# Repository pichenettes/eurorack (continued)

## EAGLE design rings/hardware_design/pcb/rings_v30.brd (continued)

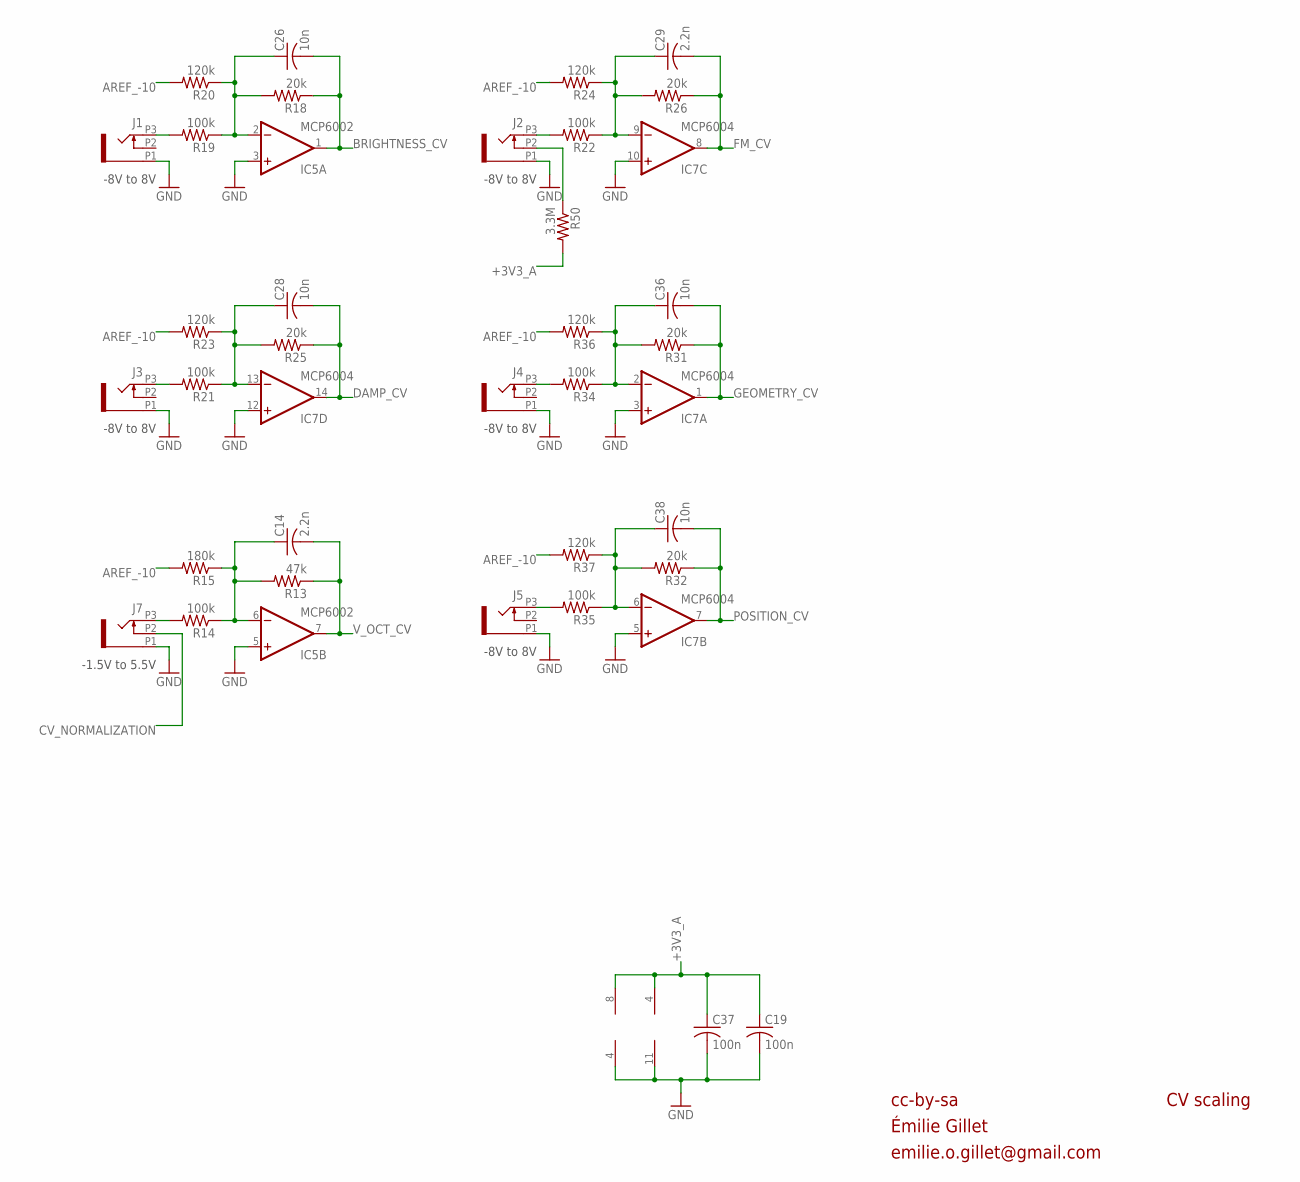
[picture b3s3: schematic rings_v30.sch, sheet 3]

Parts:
C14, C29: 2.2n; C0603
C19, C37: 100n; C0603
C26, C28, C36, C38: 10n; C0603
IC5: MCP6002; SO08
IC7: MCP6004; SO14
J1, J2, J3, J4, J5, J7: PJ301_THONKICONN6; WQP_PJ_301M6
R13: 47k; R0603
R14, R19, R21, R22, R34, R35: 100k; R0603
R15: 180k; R0603
R18, R25, R26, R31, R32: 20k; R0603
R20, R23, R24, R36, R37: 120k; R0603
R50: 3.3M; R0603

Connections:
+3V3_A: C19.1, C37.1, IC5.8 (V+), IC7.4 (V+), R50.2; also elsewhere on the board
AREF_-10: R15.2, R20.2, R23.2, R24.2, R36.2, R37.2; also elsewhere on the board
BRIGHTNESS_CV: C26.2, IC5.1 (OUT), R18.1; also elsewhere on the board
CV_NORMALIZATION: J7.P2 (2); also elsewhere on the board
DAMP_CV: C28.2, IC7.14 (OUT), R25.1; also elsewhere on the board
FM_CV: C29.2, IC7.8 (OUT), R26.1; also elsewhere on the board
GEOMETRY_CV: C36.2, IC7.1 (OUT), R31.1; also elsewhere on the board
GND: C19.2, C37.2, IC5.3 (+IN), IC5.4 (V-), IC5.5 (+IN), IC7.3 (+IN), IC7.5 (+IN), IC7.10 (+IN), IC7.11 (V-), IC7.12 (+IN), J1.P1 (1), J2.P1 (1), J3.P1 (1), J4.P1 (1), J5.P1 (1), J7.P1 (1); also elsewhere on the board
unnamed: J1.P3 (3), R19.2
unnamed: C26.1, IC5.2 (-IN), R18.2, R19.1, R20.1
unnamed: J7.P3 (3), R14.2
unnamed: J2.P3 (3), R22.2
unnamed: C29.1, IC7.9 (-IN), R22.1, R24.1, R26.2
unnamed: J4.P3 (3), R34.2
unnamed: J3.P3 (3), R21.2
unnamed: C28.1, IC7.13 (-IN), R21.1, R23.1, R25.2
unnamed: C14.1, IC5.6 (-IN), R13.2, R14.1, R15.1
unnamed: C36.1, IC7.2 (-IN), R31.2, R34.1, R36.1
unnamed: J5.P3 (3), R35.2
unnamed: C38.1, IC7.6 (-IN), R32.2, R35.1, R37.1
unnamed: J2.P2 (2), R50.1
POSITION_CV: C38.2, IC7.7 (OUT), R32.1; also elsewhere on the board
V_OCT_CV: C14.2, IC5.7 (OUT), R13.1; also elsewhere on the board

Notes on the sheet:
cc-by-sa
CV scaling
-8V to 8V
-1.5V to 5.5V
Émilie Gillet
emilie.o.gillet@gmail.com

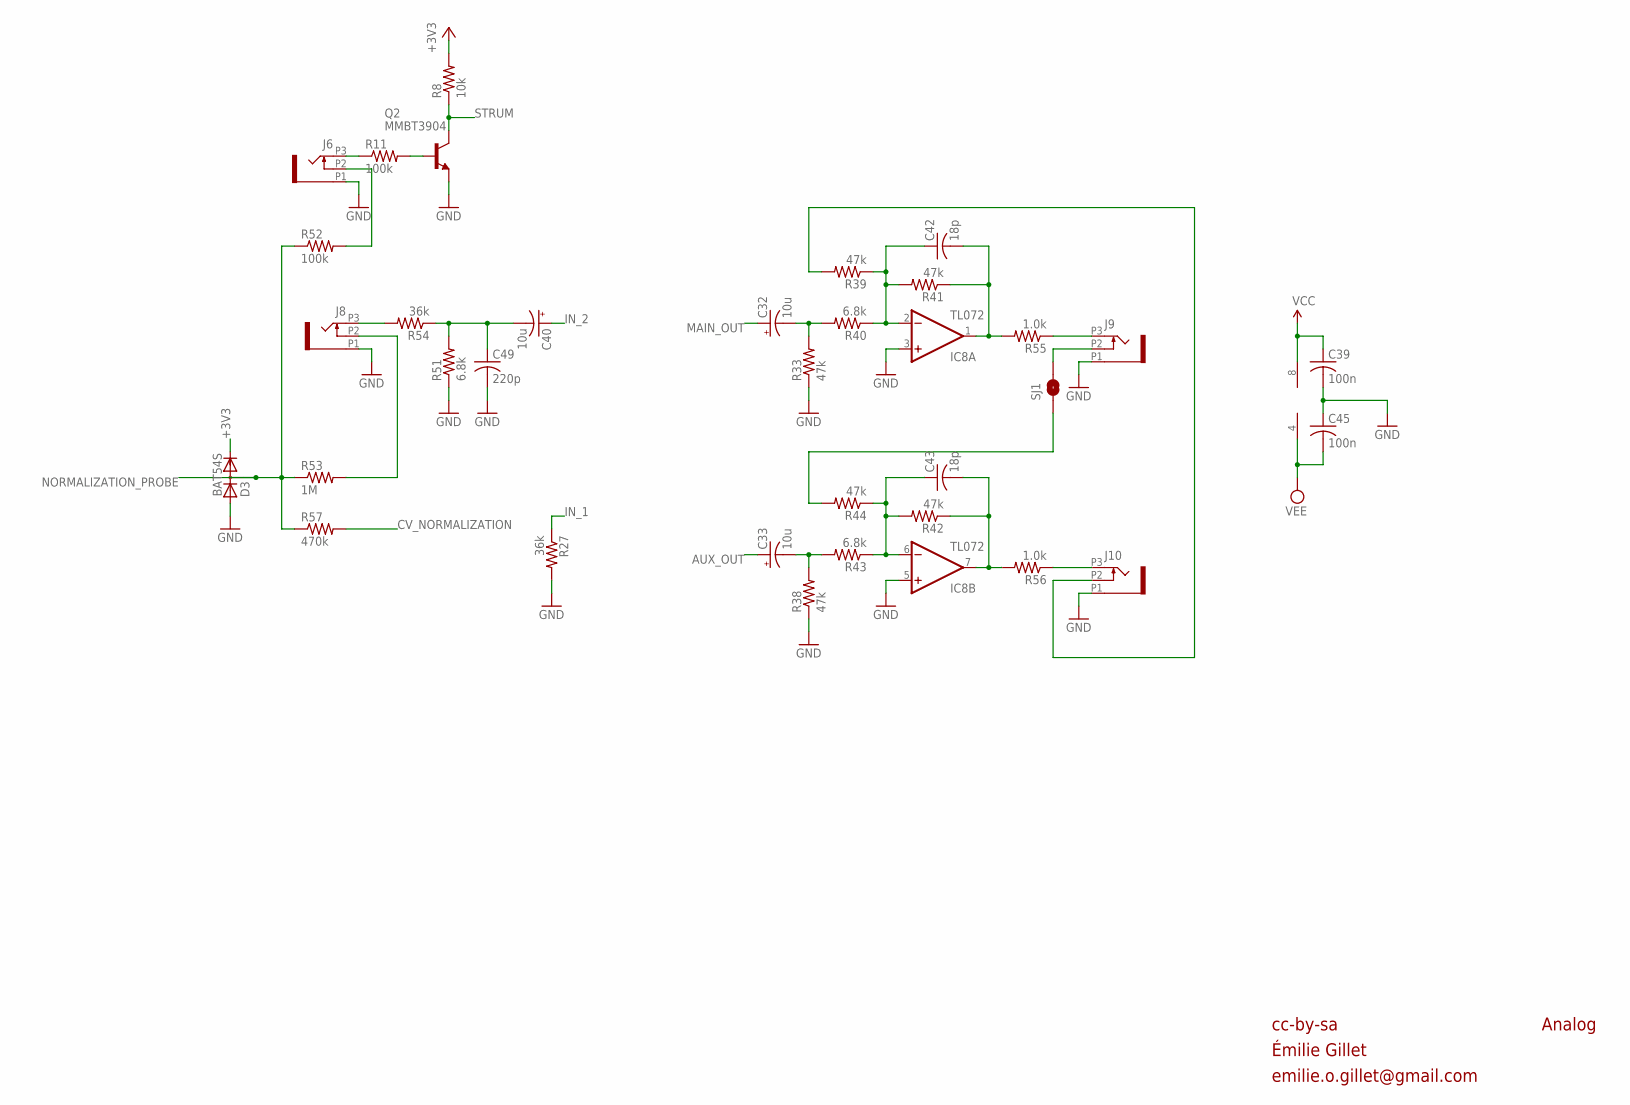
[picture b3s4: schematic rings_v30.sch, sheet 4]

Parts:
C32, C33, C40: 10u; PANASONIC_A
C39, C45: 100n; C0603
C42, C43: 18p; C0603
C49: 220p; C0603
D3: BAT54S; SOT23
IC8: TL072; SO08
J6, J8, J9, J10: PJ301_THONKICONN6; WQP_PJ_301M6
Q2: MMBT3904; SOT23-BEC
R8: 10k; R0603
R11, R52: 100k; R0603
R27, R54: 36k; R0603
R33, R38, R39, R41, R42, R44: 47k; R0603
R40, R43, R51: 6.8k; R0603
R53: 1M; R0603
R55, R56: 1.0k; R0603
R57: 470k; R0603
SJ1: SOLDERJUMPERNC2; SJ_2S-NOTRACE

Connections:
+3V3: D3.2 (C), R8.2; also elsewhere on the board
AUX_OUT: C33.+; also elsewhere on the board
CV_NORMALIZATION: R57.2; also elsewhere on the board
GND: C39.2, C45.1, C49.2, D3.1 (A), IC8.3 (+IN), IC8.5 (+IN), J6.P1 (1), J8.P1 (1), J9.P1 (1), J10.P1 (1), Q2.E, R27.2, R33.1, R38.1, R51.1; also elsewhere on the board
IN_1: R27.1; also elsewhere on the board
IN_2: C40.+; also elsewhere on the board
MAIN_OUT: C32.+; also elsewhere on the board
unnamed: J6.P3 (3), R11.1
unnamed: C40.-, C49.1, R51.2, R54.1
unnamed: J6.P2 (2), R52.2
unnamed: J8.P3 (3), R54.2
unnamed: C33.-, R38.2, R43.2
unnamed: C43.1, IC8.6 (-IN), R42.2, R43.1, R44.1
unnamed: C43.2, IC8.7 (OUT), R42.1, R56.2
unnamed: J10.P3 (3), R56.1
unnamed: C32.-, R33.2, R40.2
unnamed: C42.1, IC8.2 (-IN), R39.1, R40.1, R41.2
unnamed: C42.2, IC8.1 (OUT), R41.1, R55.2
unnamed: J9.P3 (3), R55.1
unnamed: J8.P2 (2), R53.2
unnamed: J10.P2 (2), R39.2
unnamed: R44.2, SJ1.1
unnamed: J9.P2 (2), SJ1.2
unnamed: Q2.B, R11.2
NORMALIZATION_PROBE: D3.3 (AC), R52.1, R53.1, R57.1; also elsewhere on the board
STRUM: Q2.C, R8.1; also elsewhere on the board
VCC: C39.1, IC8.8 (V+); also elsewhere on the board
VEE: C45.2, IC8.4 (V-); also elsewhere on the board

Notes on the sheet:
cc-by-sa
Analog
Émilie Gillet
emilie.o.gillet@gmail.com

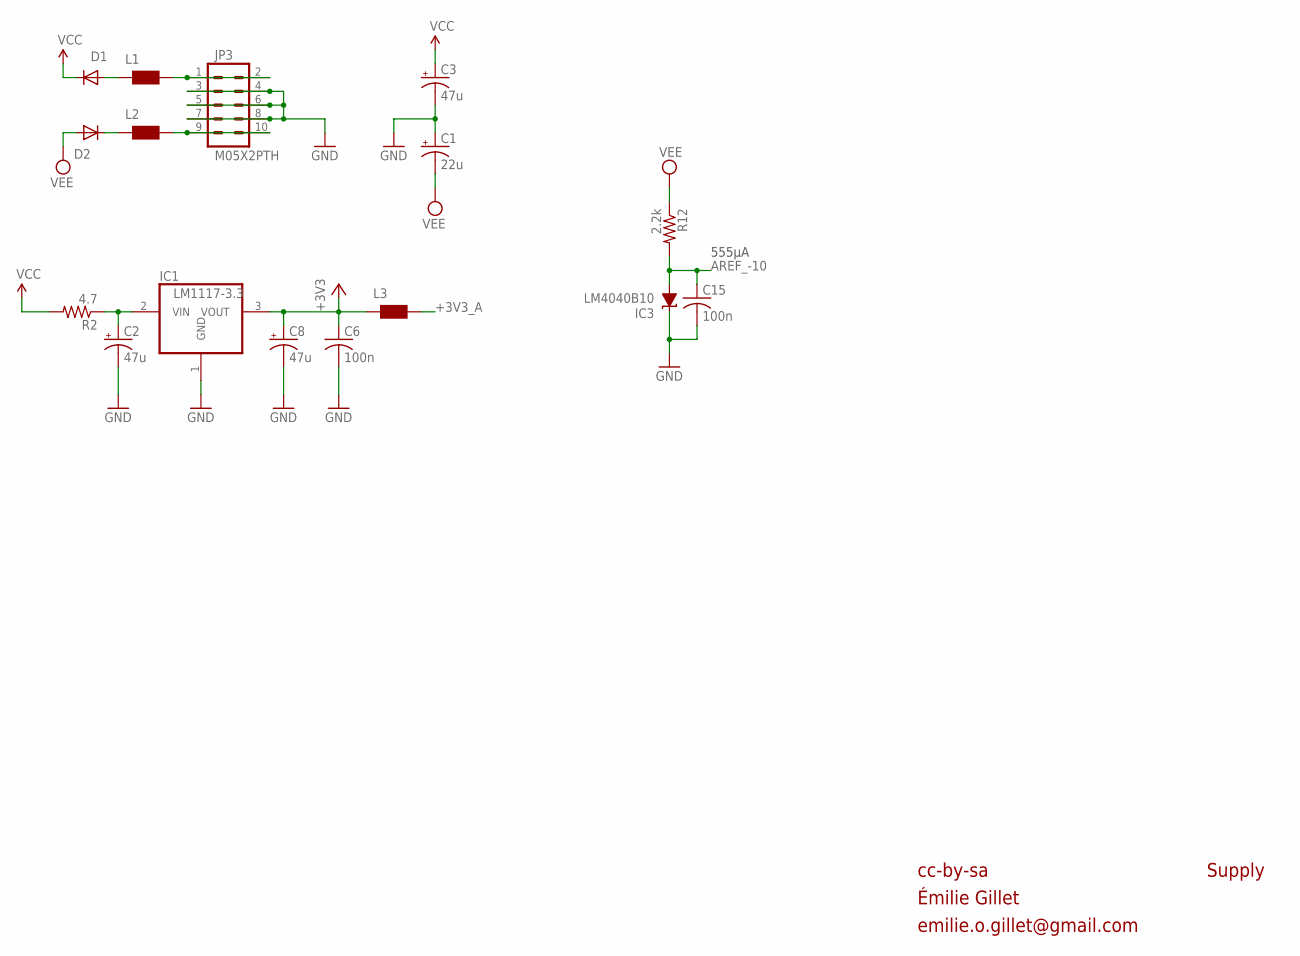
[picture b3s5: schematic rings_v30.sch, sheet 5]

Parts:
C1: 22u; PANASONIC_C
C2, C3, C8: 47u; PANASONIC_D
C6, C15: 100n; C0603
D1, D2: 1N5819HW; SOD123
IC1: LM1117-3.3; TO252
IC3: LM4040B10; DBZ_R-PDSO-G3
JP3: M05X2PTH; AVR_ICSP
L1, L2, L3: WE-CBF_0603; 0603
R2: 4.7; R1206
R12: 2.2k; R0603

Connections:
+3V3: C6.1, C8.+, IC1.3 (VOUT), L3.1; also elsewhere on the board
+3V3_A: L3.2; also elsewhere on the board
AREF_-10: C15.1, IC3.2 (A), R12.2; also elsewhere on the board
GND: C1.+, C2.-, C3.-, C6.2, C8.-, C15.2, IC1.1 (GND), IC3.1 (C), JP3.3, JP3.4, JP3.5, JP3.6, JP3.7, JP3.8; also elsewhere on the board
unnamed: C2.+, IC1.2 (VIN), R2.1
unnamed: D1.A, L1.1
unnamed: D2.C, L2.1
unnamed: JP3.1, JP3.2, L1.2
unnamed: JP3.9, JP3.10, L2.2
VCC: C3.+, D1.C, R2.2; also elsewhere on the board
VEE: C1.-, D2.A, R12.1; also elsewhere on the board

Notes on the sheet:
555µA
cc-by-sa
Supply
Émilie Gillet
emilie.o.gillet@gmail.com

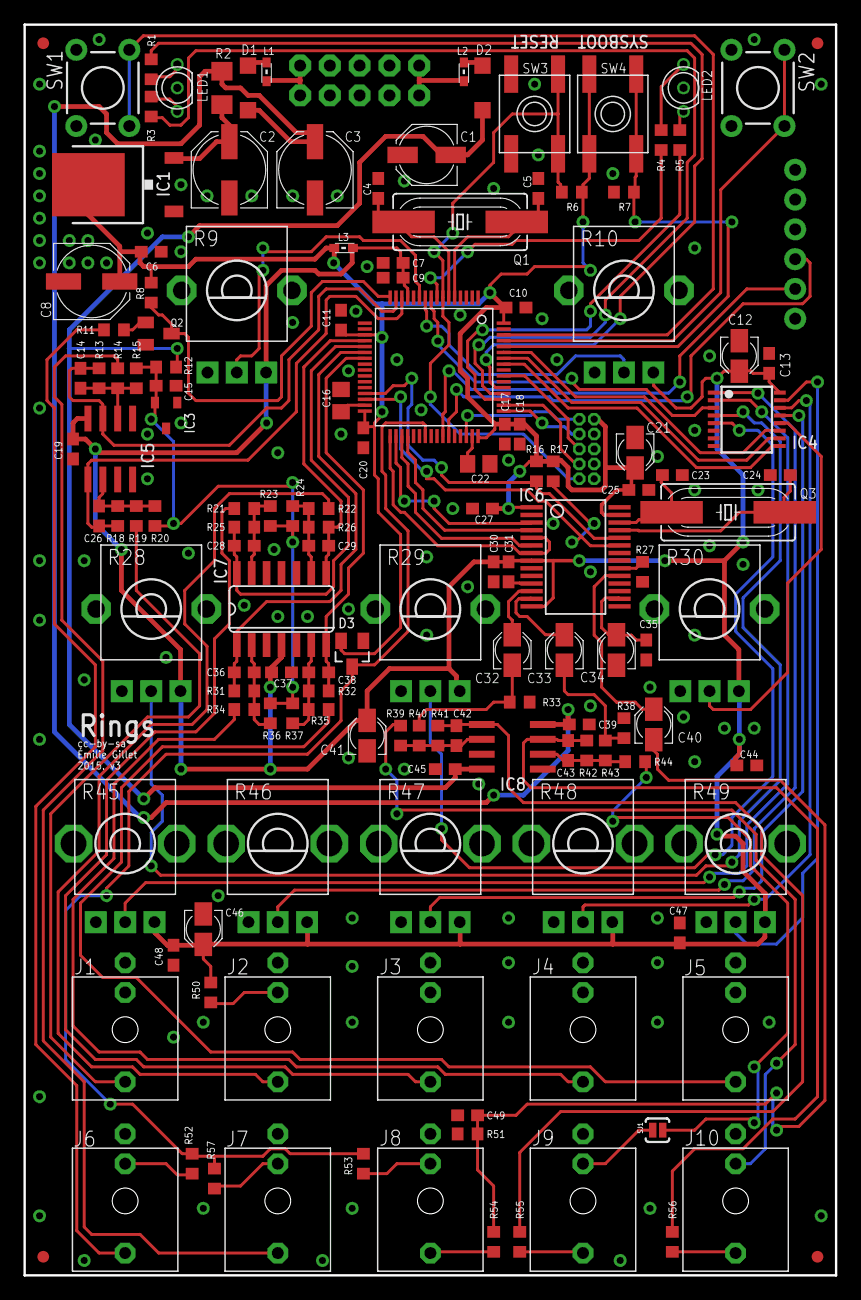
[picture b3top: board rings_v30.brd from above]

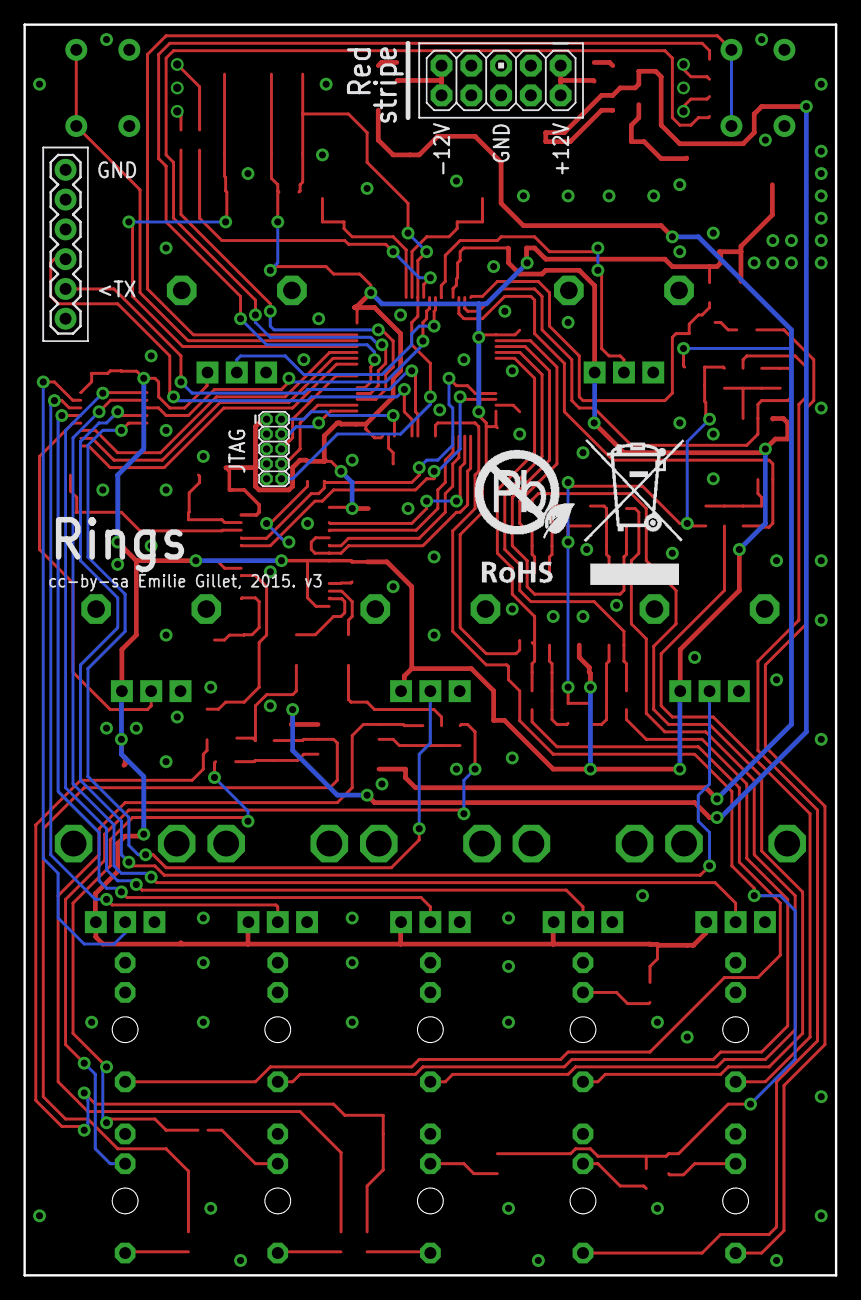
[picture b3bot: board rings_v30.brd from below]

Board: 2 copper layers, 69.2 x 106.7 mm, 148 parts (4 on the bottom side), 99 nets.

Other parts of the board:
U$2: ROHS_BIG

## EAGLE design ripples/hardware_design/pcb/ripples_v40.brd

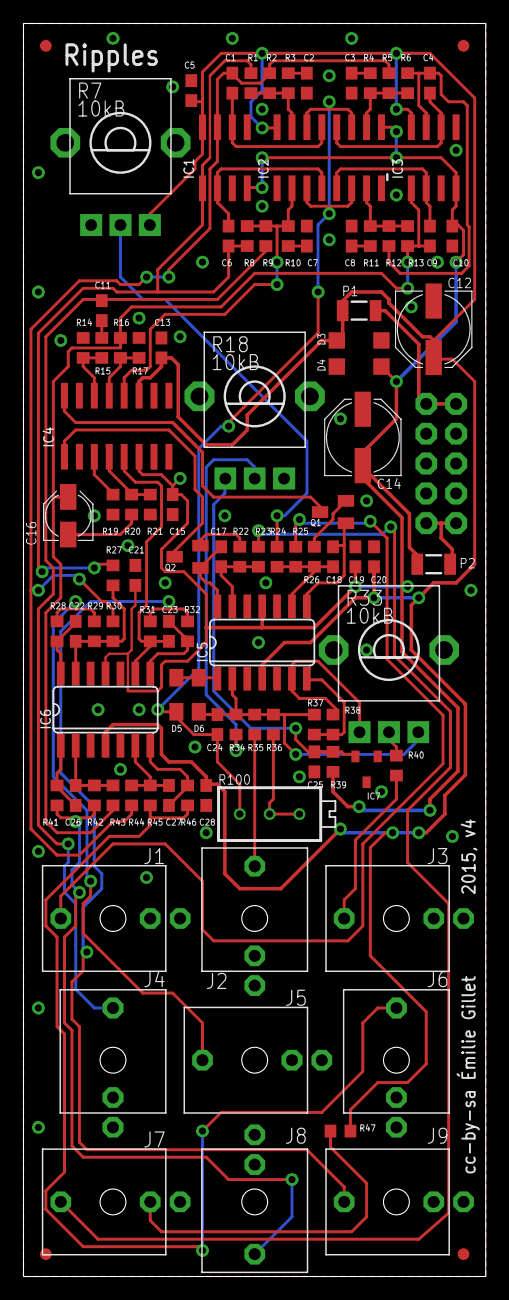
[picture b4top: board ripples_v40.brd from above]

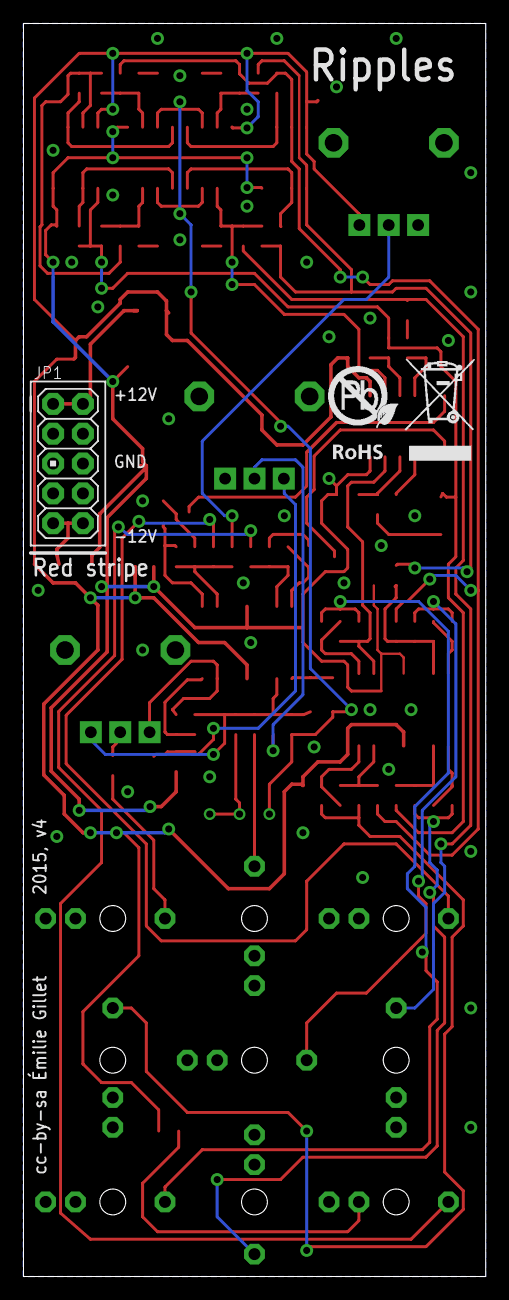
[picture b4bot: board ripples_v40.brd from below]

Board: 2 copper layers, 39.4 x 106.7 mm, 106 parts (2 on the bottom side), 63 nets.

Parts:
C1, C4, C6, C9: 220p; C0603
C2, C3, C7, C8, C17, C18, C24: 560p; C0603
C5, C10, C13, C15, C19, C20, C21, C28: 100n; C0603
C11, C25: 220n; C0603
C12, C14: 47u; PANASONIC_D
C16: 4.7u; PANASONIC_B
C22, C23, C26, C27: 47p; C0603
D3, D4: 1N5819HW; SOD123
D5, D6: 1N4148; SOD323-W
F1, F2, F3, F4: FIDUCIAL1X2; FIDUCIAL-1X2
IC1, IC3: TL072D; SO08
IC2: V2164; SOIC16N
IC4: LM13700M; SO16
IC5, IC6: TL074D; SO14
IC7: LM4040 5.0V; DBZ_R-PDSO-G3
J1, J2, J3, J4, J5, J6, J7, J8, J9: PJ301_THONKICONN6; WQP_PJ_301M6
JP1: M05X2PTH; AVR_ICSP
P1, P2: PTCSMD; PTC-1206
Q1, Q2: MMBT3906; SOT23-BEC
R1, R2, R5, R6, R8, R12, R13, R43: 33k; R0603
R3, R4, R10, R11: 510; R0603
R7, R18, R33: 10kB; ALPS_POT_VERTICAL_PS
R9, R20, R29, R31, R35, R37, R38, R40, R42, R45: 100k; R0603
R14, R17, R19, R21, R28, R32, R41, R46: 1.0k; R0603
R15: 300k; R0603
R16, R25: 22k; R0603
R22, R26, R34: 47k; R0603
R23: 27k; R0603
R24: 62k; R0603
R27, R30, R44: 39k; R0603
R36, R47: 15k; R0603
R39: 6.8k; R0603
R100: 5k; RTRIM3296X
U$2: ROHS

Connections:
BP2_OUT: J5.P3, R28.2, R29.2
CV_F_POT: R18.P$2, R34.1
CV_MOD: J3.P3, R40.1
CV_VOCT: J2.P3, R35.1
F_CV: C24.1, D5.C, IC2.3, IC2.6, IC2.11, IC2.14, R100.1
GND: C2.2, C3.2, C5.2, C7.2, C8.2, C10.1, C12.-, C13.2, C14.+, C15.1, C19.1, C20.2, C21.1, C25.2, C28.2, D3.A, D4.C, IC1.3, IC1.5, IC2.8, IC3.3, IC3.5, IC5.3, IC5.5, IC5.10, IC5.12, IC6.3, IC6.5, IC6.10, IC6.12, IC7.1, J1.P1, J2.P1, J3.P1, J4.P1, J5.P1, J6.P1, J7.P1, J8.P1, J9.P1, JP1.3, JP1.4, JP1.5, JP1.6, JP1.7, JP1.8, R7.P$3, R14.1, R17.2, R18.P$1, R19.1, R21.1
IN: C11.2, J4.P3, R9.1
I_RESO: IC4.16, Q1.C
I_VCA: IC4.1, Q2.C
LP1: C6.2, IC1.1, R1.1, R8.2, R27.1
LP2: C1.2, IC1.7, R2.2, R5.1, R30.1, R44.1
LP2_OUT: J6.P3, R45.2, R46.2
LP3: C4.2, IC3.7, R6.2, R12.1
LP4: C9.2, C16.+, IC3.1, R13.2, R16.2, R43.1
LP4_OUT: J8.P3, R41.2, R42.2
LP4_VCA_OUT: J9.P3, R31.2, R32.2
unnamed: IC5.7, R37.1, R38.2
unnamed: C6.1, IC1.2, IC2.4
unnamed: IC2.15, R1.2, R2.1, R3.2
unnamed: R36.2, R100.2, R100.3
unnamed: IC4.3, R19.2
unnamed: JP1.1, JP1.2, P1.2
unnamed: C11.1, R15.2
unnamed: C7.1, R10.1
unnamed: C1.1, IC1.6, IC2.13
unnamed: IC2.2, IC4.12, R8.1, R9.2, R10.2
unnamed: C2.1, R3.1
unnamed: IC2.10, R4.2, R5.2, R6.1
unnamed: C4.1, IC2.12, IC3.6
unnamed: IC4.13, R16.1, R17.1
unnamed: C3.1, R4.1
unnamed: IC2.7, R11.2, R12.2, R13.1
unnamed: C9.1, IC2.5, IC3.2
unnamed: IC4.14, R14.2, R15.1
unnamed: C8.1, R11.1
unnamed: JP1.9, JP1.10, P2.2
unnamed: R33.P$2, R40.2
unnamed: IC5.6, R33.P$3, R38.1
unnamed: C24.2, D6.A, IC5.2, R33.P$1, R34.2, R35.2, R36.1, R37.2
unnamed: R7.P$2, R24.1
unnamed: C17.2, IC5.13, R22.1, R23.2
unnamed: C18.2, IC5.9, R24.2, R25.2, R26.1
unnamed: C18.1, IC5.8, Q1.B
unnamed: Q1.E, R26.2
unnamed: J7.P2, R47.1
unnamed: C17.1, IC5.14, Q2.B
unnamed: Q2.E, R22.2
unnamed: C27.1, IC6.6, R44.2, R45.1
unnamed: C26.1, IC6.2, R42.1, R43.2
unnamed: C26.2, IC6.1, R41.1
unnamed: D5.A, D6.C, IC5.1
unnamed: C27.2, IC6.7, R46.1
unnamed: C22.1, IC6.13, R27.2, R29.1, R30.2
unnamed: C22.2, IC6.14, R28.1
unnamed: IC4.4, R20.2, R21.2
unnamed: C23.1, IC4.5, IC6.9, R31.1
unnamed: C23.2, IC6.8, R32.1
unnamed: C16.-, R20.1
Q_CV: J1.P3, R25.1
REF_-5: C25.1, IC7.2, R18.P$3, R39.2
VCA_CV: J7.P3, R23.1
VCC: C5.1, C12.+, C13.1, C20.1, C28.1, D3.C, IC1.8, IC2.16, IC3.8, IC4.11, IC5.4, IC6.4, P1.1, R7.P$1, R47.2
VEE: C10.2, C14.-, C15.2, C19.2, C21.2, D4.A, IC1.4, IC2.9, IC3.4, IC4.6, IC5.11, IC6.11, P2.1, R39.1

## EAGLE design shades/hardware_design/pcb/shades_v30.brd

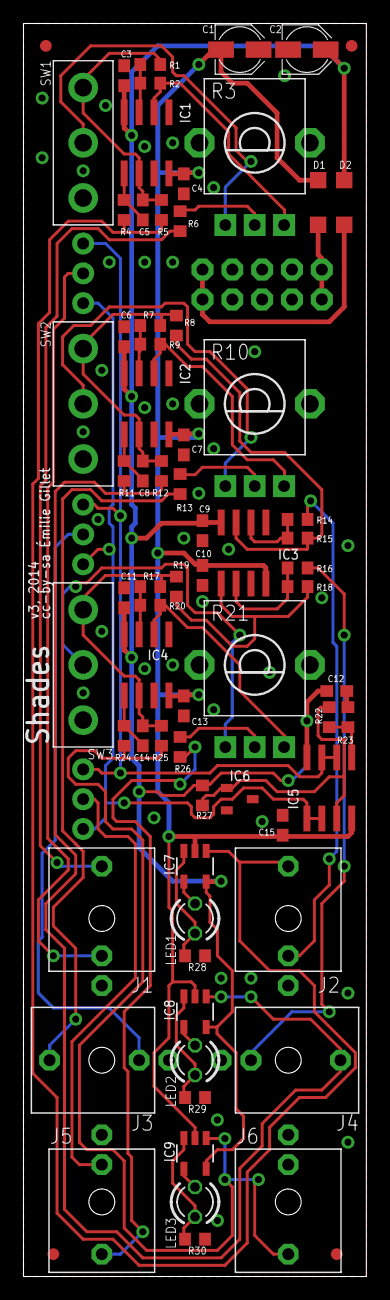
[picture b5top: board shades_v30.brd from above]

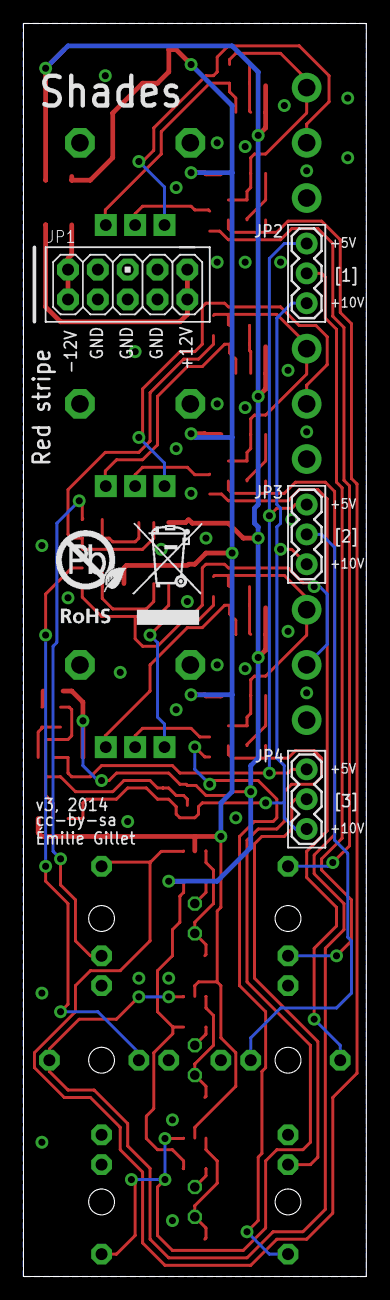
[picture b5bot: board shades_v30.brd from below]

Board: 2 copper layers, 29.2 x 106.7 mm, 77 parts (5 on the bottom side), 48 nets.

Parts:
C1, C2: 10u; PANASONIC_B
C3, C4, C6, C7, C9, C10, C11, C12, C13, C15: 100n; C0603
C5, C8, C14: 22p; C0603
D1, D2: 1N5819HW; SOD123
F1, F2, F3, F4: FIDUCIAL1X2; FIDUCIAL-1X2
IC1, IC2, IC3, IC4: LME49720; SO08
IC5: TL072; SO08
IC6: LM4040 10V; DBZ_R-PDSO-G3
IC7, IC8, IC9: LM321MF; SOT23-5
J1, J2, J3, J4, J5, J6: PJ301_THONKICONN6; WQP_PJ_301M6
JP1: M05X2PTH; AVR_ICSP
JP2, JP3, JP4: 1X03
LED1, LED2, LED3: WP937EGW; LED3MM
R1, R2, R5, R6, R7, R8, R9, R12, R13, R14, R15, R16, R17, R18, R19, R20, R22, R23, R25, R26: 100k; R0603
R3, R10, R21: 10kB; ALPS_POT_VERTICAL_PS
R4, R11, R24, R28, R29, R30: 1.0k; R0603
R27: 10k; R0603
SW1, SW2, SW3: ES_100SP1T6B11M2QEH_SMALL
U$2: ROHS

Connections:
GND: C1.+, C2.-, C3.2, C4.1, C6.2, C7.1, C9.2, C10.1, C11.2, C12.2, C13.1, C15.1, IC1.3, IC1.5, IC2.3, IC2.5, IC3.3, IC3.5, IC4.3, IC4.5, IC6.2, J1.P1, J2.P1, J3.P1, J4.P1, J5.P1, J6.P1, JP1.3, JP1.4, JP1.5, JP1.6, JP1.7, JP1.8, R23.1, R28.2, R29.2, R30.2, SW1.S, SW2.S, SW3.S
unnamed: J1.P2, JP2.2
unnamed: J3.P2, JP3.2
unnamed: J5.P2, JP4.2
unnamed: IC7.3, LED1.A, R28.1
unnamed: IC5.5, R22.1, R23.2
unnamed: D2.A, JP1.1, JP1.2
unnamed: IC7.4, LED1.K
unnamed: J1.P3, R6.1
unnamed: R3.P$2, R6.2
unnamed: R3.P$3, SW1.P
unnamed: C5.1, IC1.2, R1.2, R5.1, SW1.O
unnamed: IC1.6, R2.1, R3.P$1
unnamed: IC1.7, R1.1, R2.2
unnamed: C5.2, IC1.1, R4.1
unnamed: J3.P3, R13.1
unnamed: IC8.3, LED2.A, R29.1
unnamed: R10.P$2, R13.2
unnamed: R10.P$3, SW2.P
unnamed: D1.C, JP1.9, JP1.10
unnamed: IC2.6, R9.1, R10.P$1
unnamed: IC2.7, R7.1, R9.2
unnamed: IC8.4, LED2.K
unnamed: C8.2, IC2.1, R11.1
unnamed: J5.P3, R26.1
unnamed: R21.P$2, R26.2
unnamed: IC4.6, R20.1, R21.P$1
unnamed: IC4.7, R17.1, R20.2
unnamed: C14.2, IC4.1, R24.1
unnamed: IC9.3, LED3.A, R30.1
unnamed: IC9.4, LED3.K
unnamed: IC3.6, R14.2, R15.1
unnamed: IC3.2, R16.2, R18.1
unnamed: IC3.1, R18.2, R19.1
unnamed: IC3.7, R8.1, R15.2
unnamed: C14.1, IC4.2, R17.2, R19.2, R25.1, SW3.O
unnamed: C8.1, IC2.2, R7.2, R8.2, R12.1, SW2.O
OUT_1: IC7.1, J2.P3, R4.2, R5.2
OUT_2: IC8.1, J4.P3, R11.2, R12.2
OUT_3: IC9.1, J6.P3, R24.2, R25.2
REF_5: IC5.6, IC5.7, JP2.3, JP3.3, JP4.3
REF_10: IC5.1, IC5.2, JP2.1, JP3.1, JP4.1
REF_10_UNBUF: IC5.3, IC6.1, R22.2, R27.2
SEND_1: J2.P2, R14.1
SEND_2: J4.P2, R16.1
SW3: R21.P$3, SW3.P
VCC: C2.+, C3.1, C6.1, C9.1, C11.1, C12.1, D2.C, IC1.8, IC2.8, IC3.8, IC4.8, IC5.8, IC7.5, IC8.5, IC9.5, R27.1
VEE: C1.-, C4.2, C7.2, C10.2, C13.2, C15.2, D1.A, IC1.4, IC2.4, IC3.4, IC4.4, IC5.4, IC7.2, IC8.2, IC9.2

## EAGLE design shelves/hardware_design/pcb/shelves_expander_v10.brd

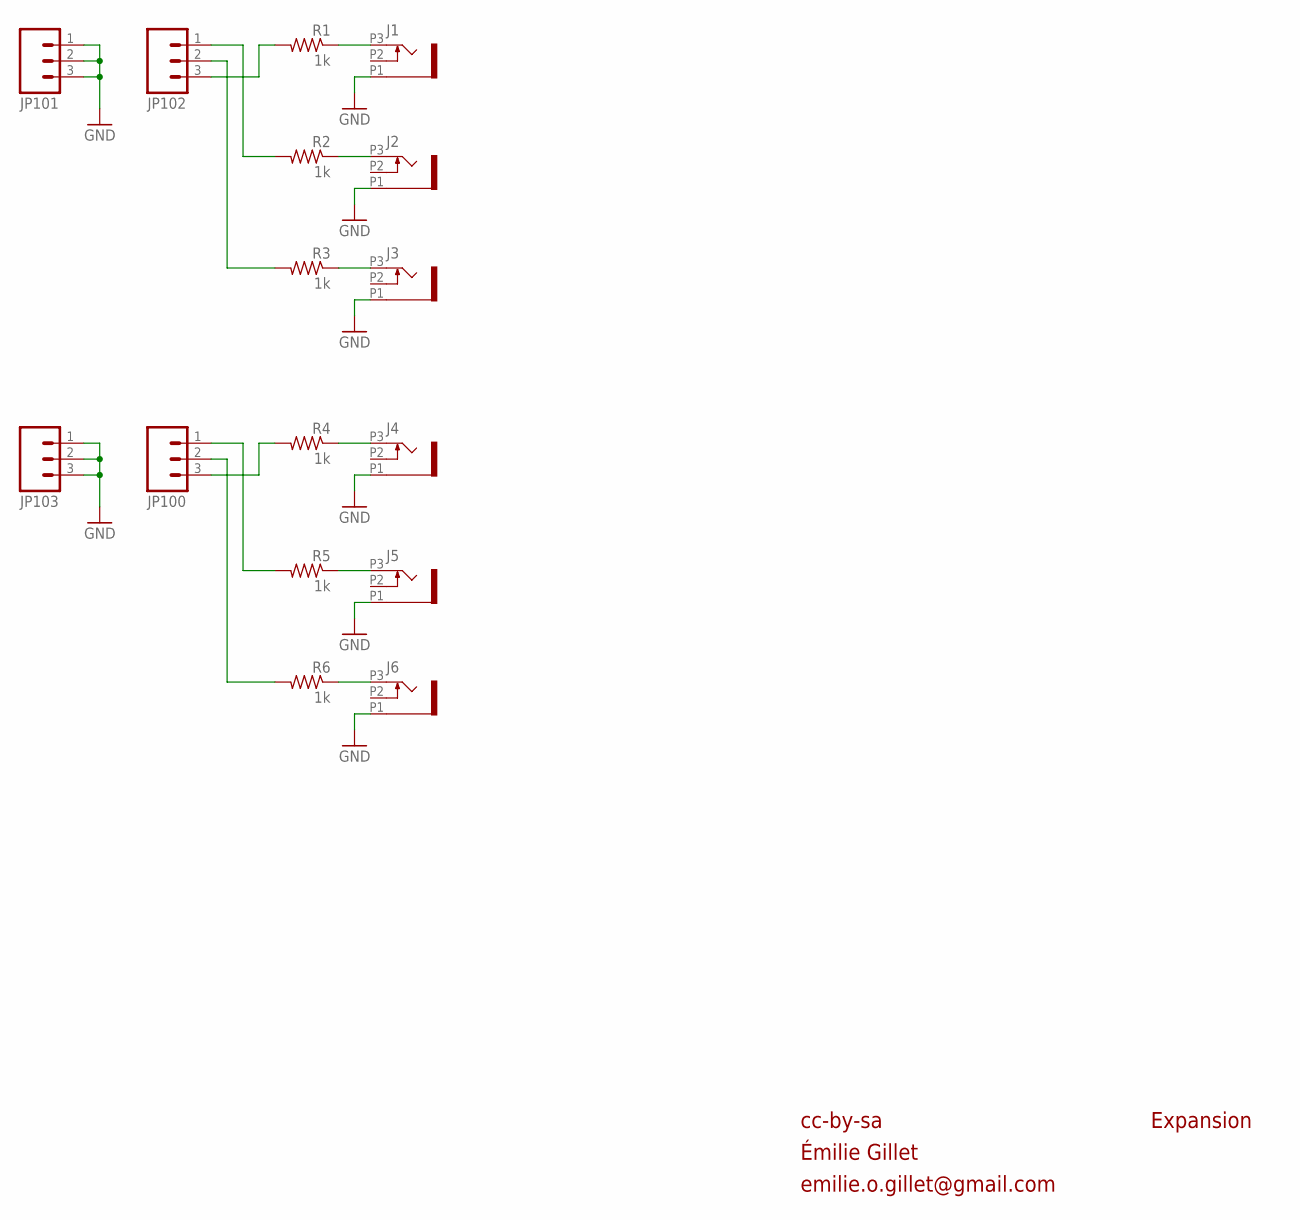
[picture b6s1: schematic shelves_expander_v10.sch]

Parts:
J1, J2, J3, J4, J5, J6: PJ301_THONKICONN6; WQP_PJ_301M6
JP100, JP101, JP102, JP103: M03PTH; 1X03
R1, R2, R3, R4, R5, R6: 1k; R0603

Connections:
BP_1: JP102.1, R2.2
BP_2: JP100.1, R5.2
GND: J1.P1 (1), J2.P1 (1), J3.P1 (1), J4.P1 (1), J5.P1 (1), J6.P1 (1), JP101.1, JP101.2, JP101.3, JP103.1, JP103.2, JP103.3
HP_1: JP102.3, R1.2
HP_2: JP100.3, R4.2
unnamed: J4.P3 (3), R4.1
unnamed: J1.P3 (3), R1.1
unnamed: J6.P3 (3), R6.1
unnamed: J2.P3 (3), R2.1
unnamed: J5.P3 (3), R5.1
unnamed: J3.P3 (3), R3.1
unnamed: JP100.2, R6.2
unnamed: JP102.2, R3.2

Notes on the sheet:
cc-by-sa
Expansion
Émilie Gillet
emilie.o.gillet@gmail.com

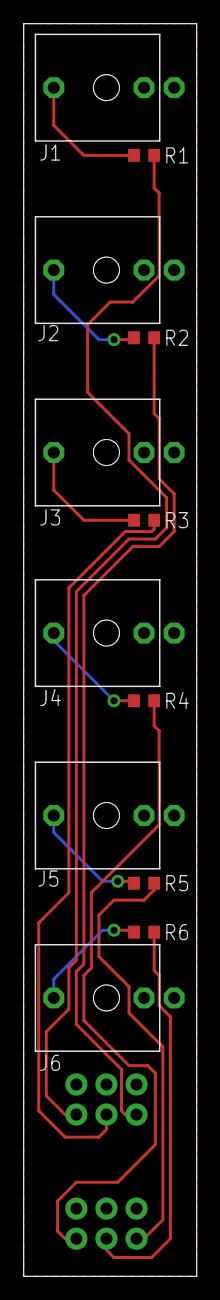
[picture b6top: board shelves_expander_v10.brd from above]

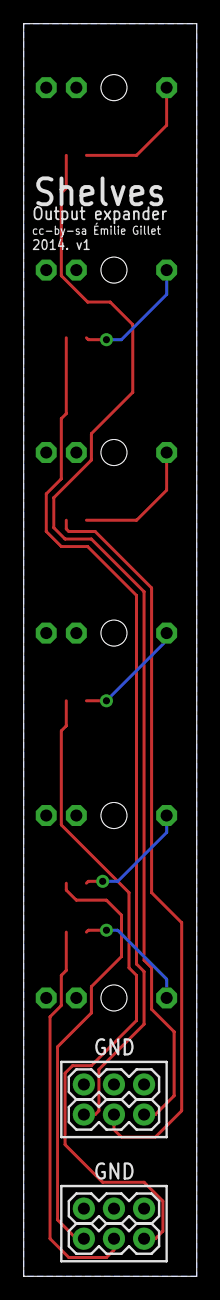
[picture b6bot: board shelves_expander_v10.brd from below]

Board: 2 copper layers, 14.6 x 105.7 mm, 16 parts (4 on the bottom side), 13 nets.

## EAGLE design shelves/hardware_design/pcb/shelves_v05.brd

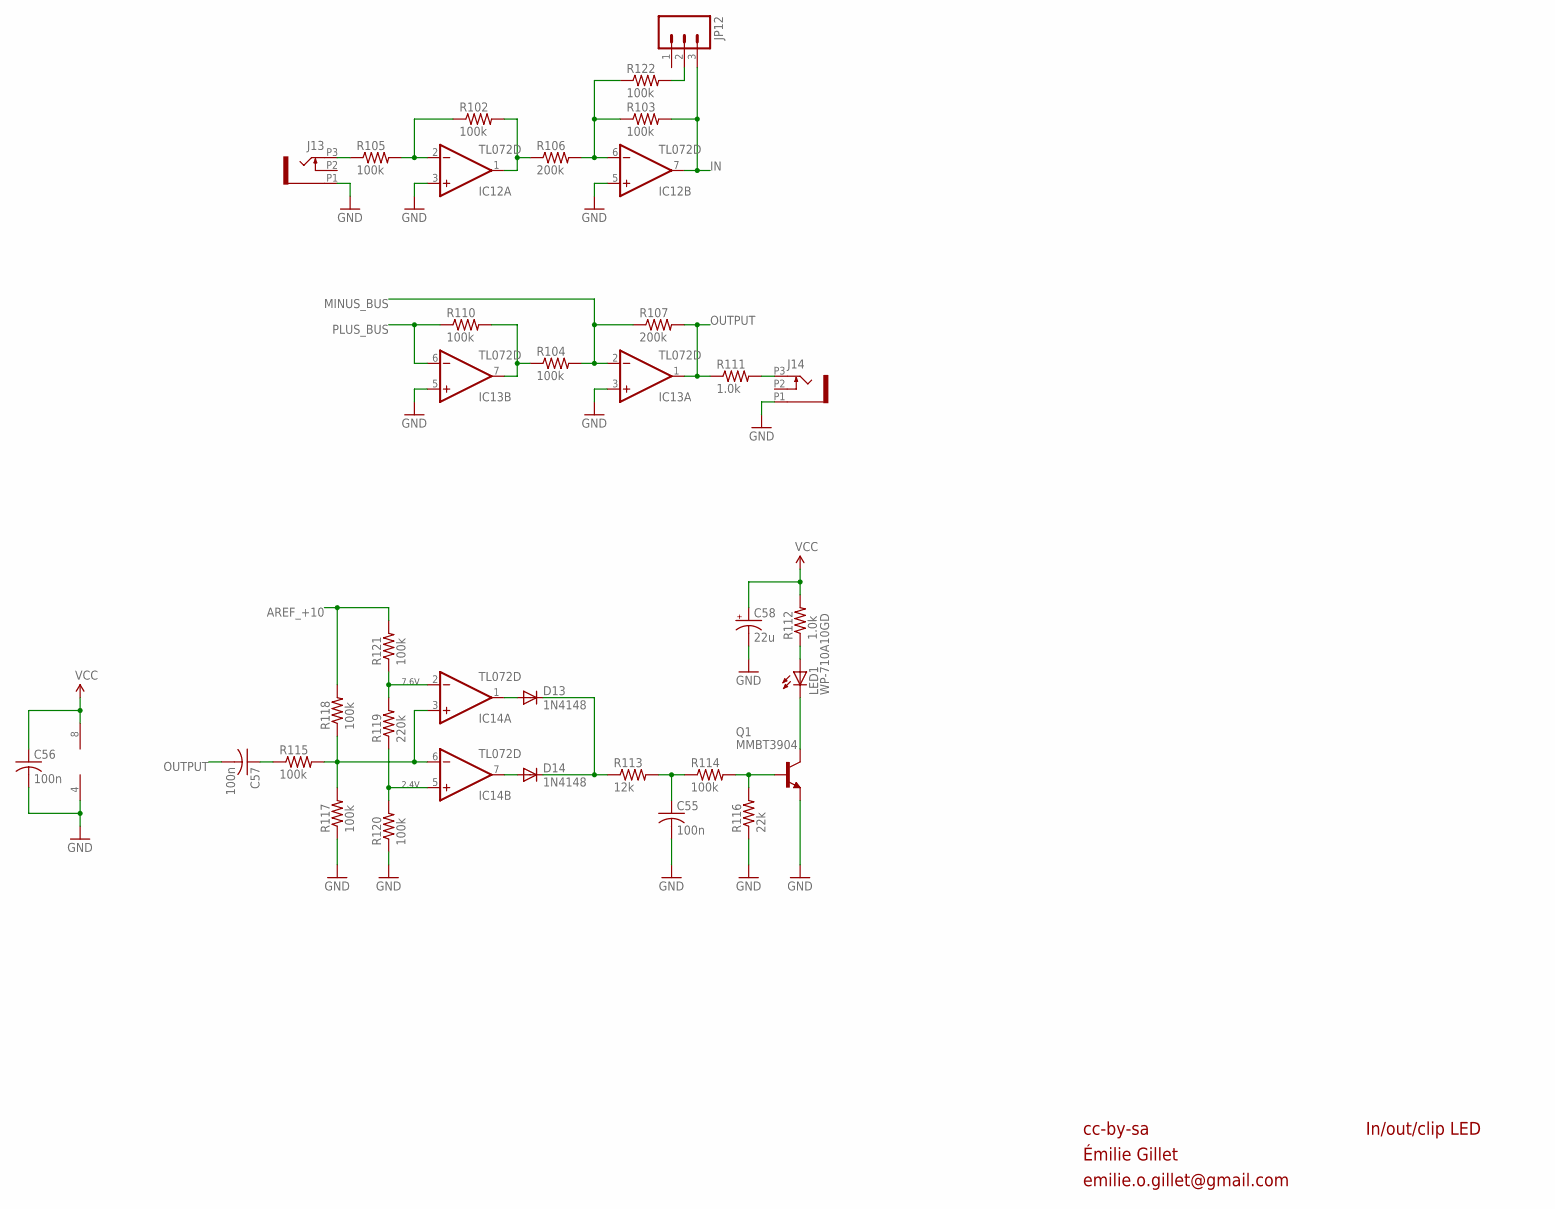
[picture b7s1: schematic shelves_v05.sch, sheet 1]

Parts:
C55, C56, C57: 100n; C0603
C58: 22u; PANASONIC_C
D13, D14: 1N4148; SOD323-W
IC12, IC13, IC14: TL072D; SO08
J13, J14: PJ301_THONKICONN6; WQP_PJ_301M6
JP12: M03PTH; 1X03
LED1: WP-710A10GD; LED3MM
Q1: MMBT3904; SOT23-BEC
R102, R103, R104, R105, R110, R114, R115, R117, R118, R120, R121, R122: 100k; R0603
R106, R107: 200k; R0603
R111, R112: 1.0k; R0603
R113: 12k; R0603
R116: 22k; R0603
R119: 220k; R0603

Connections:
AREF_+10: R118.2, R121.2; also elsewhere on the board
GND: C55.2, C56.2, C58.-, IC12.3 (+IN), IC12.5 (+IN), IC13.3 (+IN), IC13.5 (+IN), IC14.4 (V-), J13.P1 (1), J14.P1 (1), Q1.E, R116.1, R117.1, R120.1; also elsewhere on the board
IN: IC12.7 (OUT), JP12.3, R103.2; also elsewhere on the board
IN_INV: IC12.1 (OUT), R102.2, R106.1
IN_INV1: IC13.7 (OUT), R104.1, R110.2
J_IN: J13.P3 (3), R105.1
MINUS_BUS: IC13.2 (-IN), R104.2, R107.1; also elsewhere on the board
unnamed: JP12.2, R122.2
unnamed: IC12.2 (-IN), R102.1, R105.2
unnamed: IC12.6 (-IN), R103.1, R106.2, R122.1
unnamed: LED1.K (C), Q1.C
unnamed: J14.P3 (3), R111.2
unnamed: C57.1, R115.1
unnamed: IC14.3 (+IN), IC14.6 (-IN), R115.2, R117.2, R118.1
unnamed: IC14.2 (-IN), R119.2, R121.1
unnamed: C55.1, R113.2, R114.1
unnamed: IC14.5 (+IN), R119.1, R120.2
unnamed: D13.A, IC14.1 (OUT)
unnamed: D14.A, IC14.7 (OUT)
unnamed: D13.C, D14.C, R113.1
unnamed: LED1.A, R112.1
unnamed: Q1.B, R114.2, R116.2
OUTPUT: C57.2, IC13.1 (OUT), R107.2, R111.1
PLUS_BUS: IC13.6 (-IN), R110.1; also elsewhere on the board
VCC: C56.1, C58.+, IC14.8 (V+), R112.2; also elsewhere on the board

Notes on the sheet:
cc-by-sa
In/out/clip LED
2.4V
7.6V
Émilie Gillet
emilie.o.gillet@gmail.com
